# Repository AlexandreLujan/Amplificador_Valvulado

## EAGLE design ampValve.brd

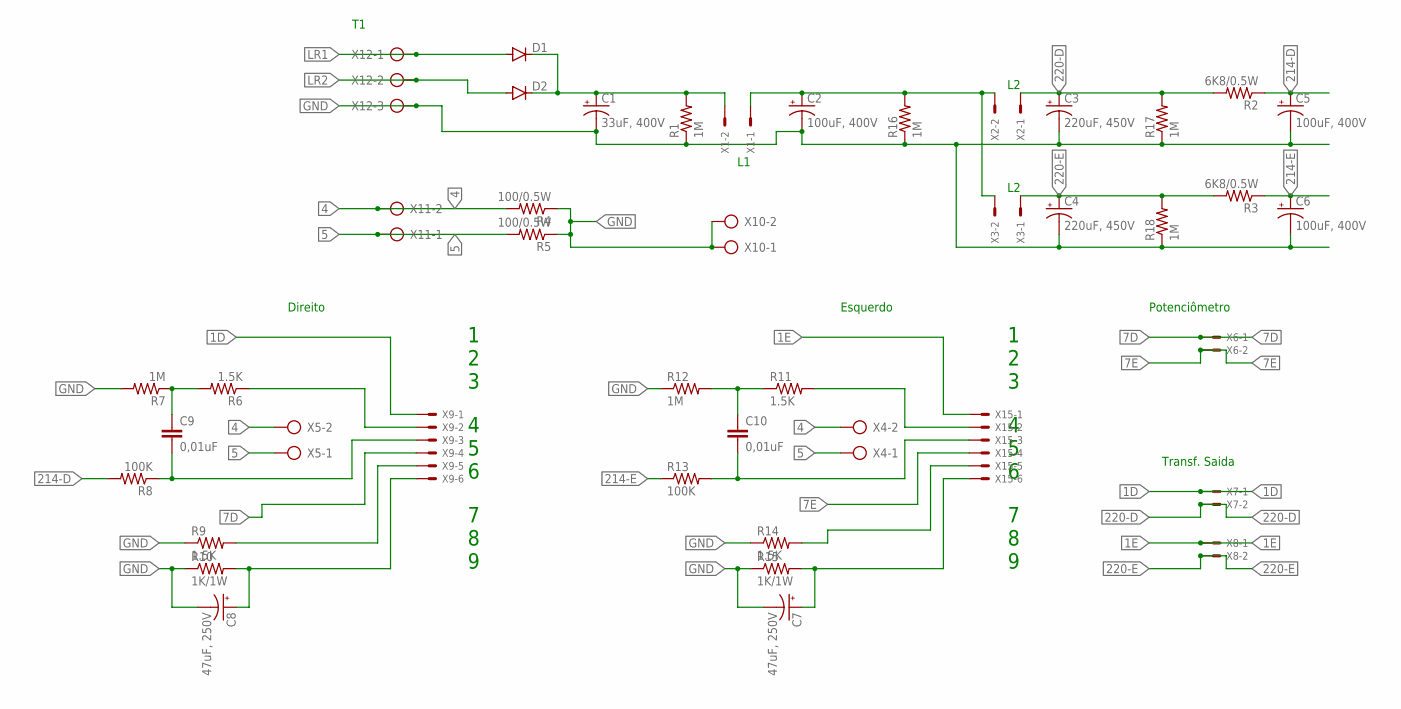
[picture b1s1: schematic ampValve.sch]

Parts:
C1: 33uF, 400V; E7,5-16
C2, C5, C6: 100uF, 400V; E7,5-18
C3, C4: 220uF, 450V; EB25D
C7, C8: 47uF, 250V; E5-13
C9, C10: 0,01uF; C102-043X133
D1, D2: DIODE-D-12.5; D-12.5
R1, R7, R12, R16, R17, R18: 1M; 0207/10
R2, R3: 6K8/0.5W; 0207/10
R4, R5: 100/0.5W; 0207/10
R6, R9, R11, R14: 1.5K; 0207/10
R8, R13: 100K; 0207/10
R10, R15: 1K/1W; 0207/10
X1, X2, X3, X6, X7, X8: KK-156-2
X4, X5, X10, X11: AK500/2-H
X9, X15: KK-156-6
X12: AK500/3-H

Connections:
1D: X7.1, X9.1
1E: X8.1, X15.1
4: R4.2, X4.2, X5.2, X11.2
5: R5.2, X4.1, X5.1, X11.1
7D: X6.1, X9.4
7E: X6.2, X15.4
214-D: C5.+, R2.1, R8.2
214-E: C6.+, R3.1, R13.1
220-D: C3.+, R2.2, R17.2, X2.1, X7.2
220-E: C4.+, R3.2, R18.2, X3.1, X8.2
GND: C1.-, C2.-, C3.-, C4.-, C5.-, C6.-, C7.-, C8.-, R1.1, R4.1, R5.1, R7.2, R9.1, R10.1, R12.1, R14.1, R15.1, R16.1, R17.1, R18.1, X10.1, X10.2, X12.3
LR1: D1.A, X12.1
LR2: D2.A, X12.2
unnamed: C1.+, D1.C, D2.C, R1.2, X1.2
unnamed: C2.+, R16.2, X1.1, X2.2, X3.2
unnamed: C9.2, R8.1, X9.3
unnamed: C10.2, R13.2, X15.3
unnamed: R14.2, X15.5
unnamed: R9.2, X9.5
unnamed: C9.1, R6.2, R7.1
unnamed: R6.1, X9.2
unnamed: C10.1, R11.1, R12.2
unnamed: R11.2, X15.2
unnamed: C7.+, R15.2, X15.6
unnamed: C8.+, R10.2, X9.6

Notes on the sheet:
1 2 3
4 5 6
7 8 9
Direito
Esquerdo
Potenciômetro
Transf. Saida

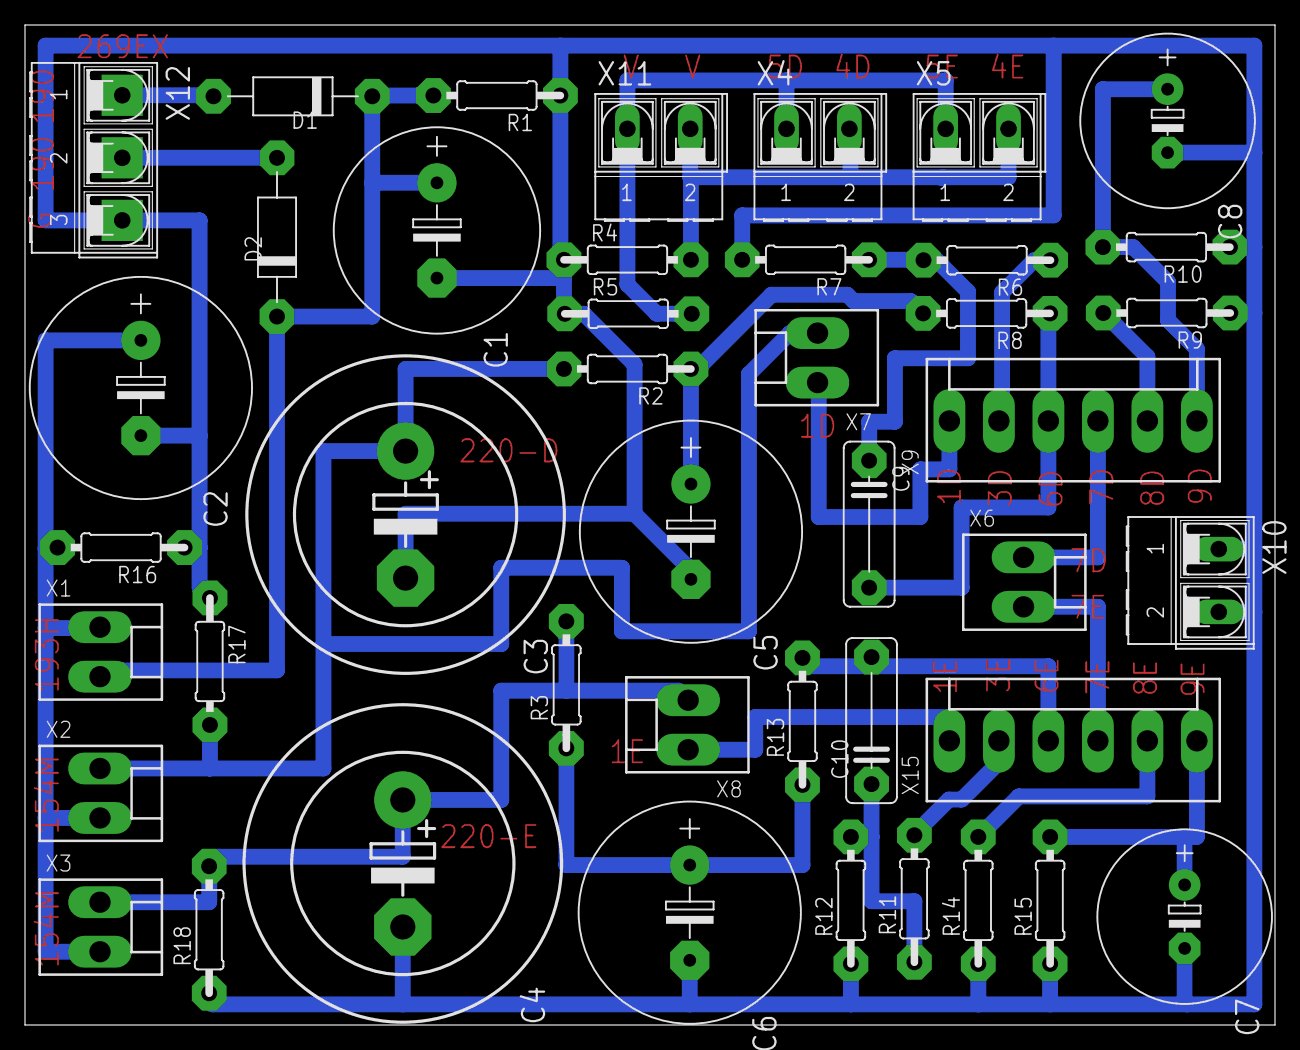
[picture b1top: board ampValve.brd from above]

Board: 2 copper layers, 100.0 x 80.0 mm, 43 parts (0 on the bottom side), 25 nets.
